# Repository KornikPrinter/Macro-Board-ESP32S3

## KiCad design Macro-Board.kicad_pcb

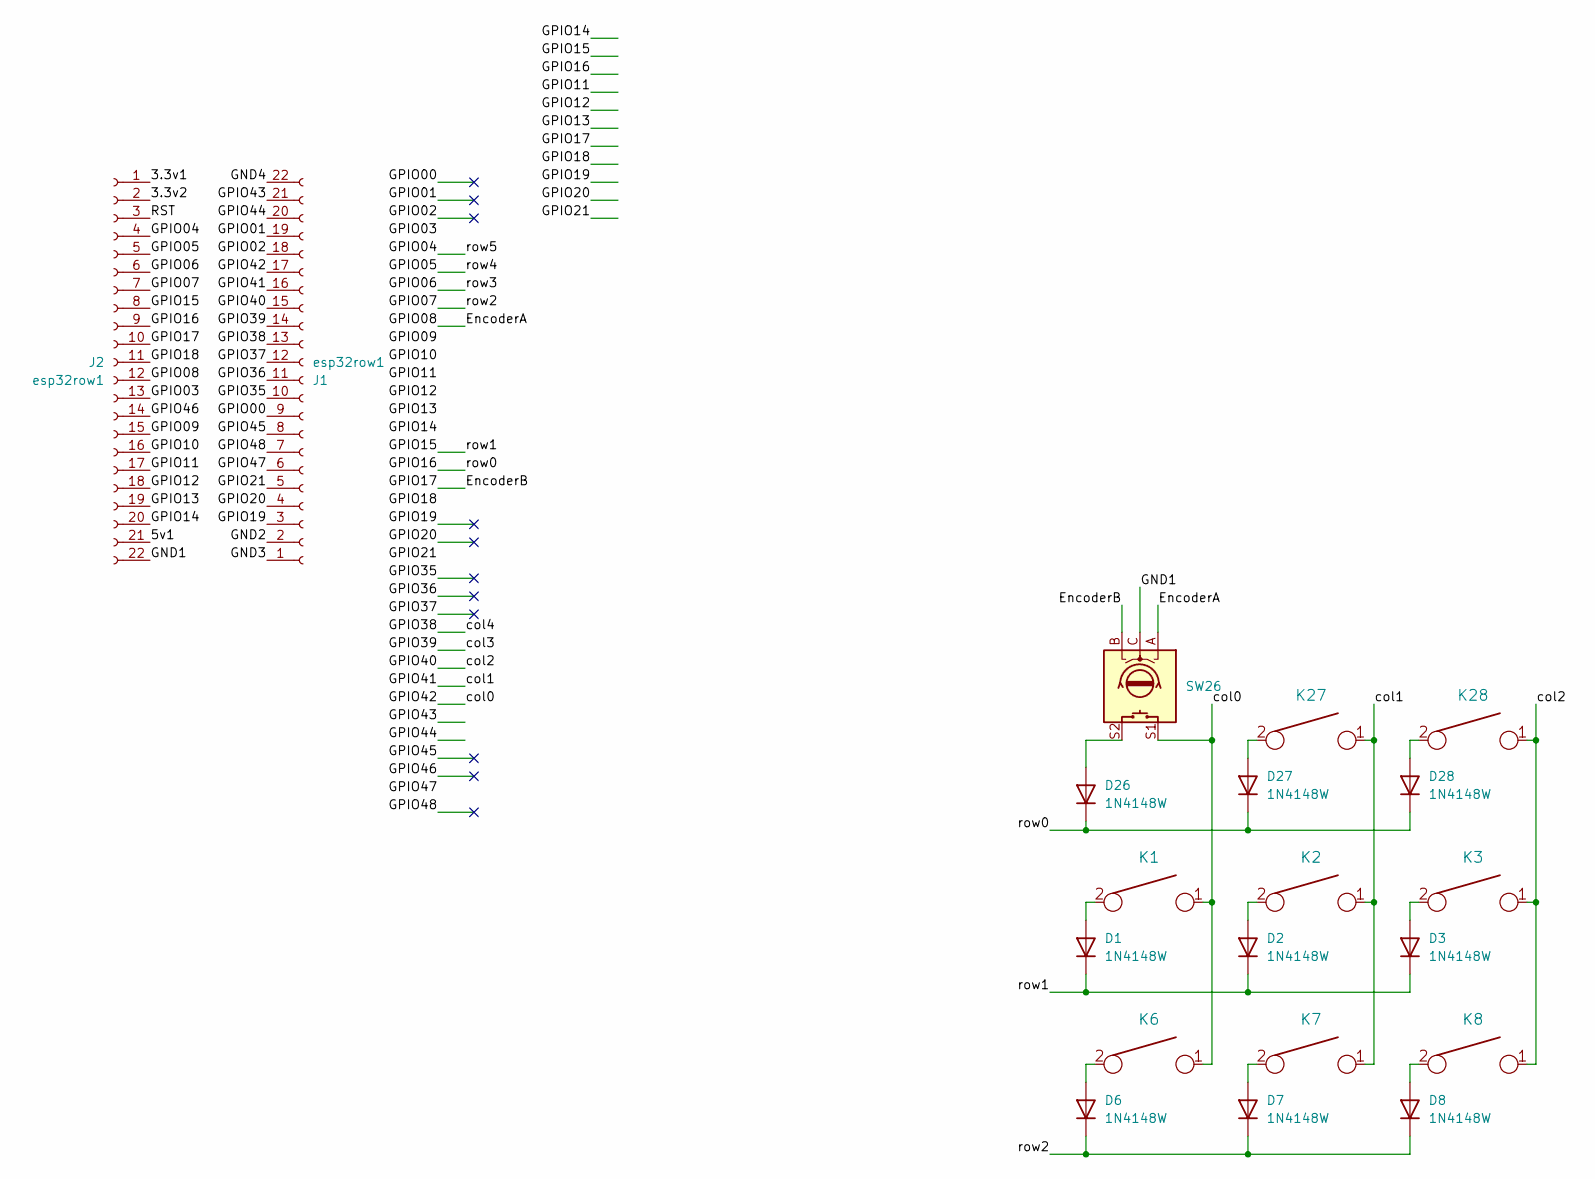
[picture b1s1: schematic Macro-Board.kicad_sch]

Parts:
D1, D2, D3, D6, D7, D8, D26, D27, D28: 1N4148W; D_SOD-123
J1, J2: esp32row1; PinSocket_1x22_P2.54mm_Vertical
K1, K2, K3, K6, K7, K8, K27, K28: KEYSW; SW_Hotswap_Kailh_MX_Plated_1.00u
SW26: RotaryEncoder_Alps_EC11E-Switch_Vertical_H20mm

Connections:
/3.3v1: J2.1
/3.3v2: J2.2
/5v1: J2.21
/EncoderA: J2.12, SW26.A
/EncoderB: J2.10, SW26.B
/GND1: J2.22, SW26.C
/GND2: J1.2
/GND3: J1.1
/GND4: J1.22
/GPIO00: J1.9
/GPIO01: J1.19
/GPIO02: J1.18
/GPIO03: J2.13
/GPIO04: J2.4
/GPIO05: J2.5
/GPIO06: J2.6
/GPIO07: D6.1 (K), D7.1 (K), D8.1 (K), J2.7
/GPIO09: J2.15
/GPIO10: J2.16
/GPIO11: J2.17
/GPIO12: J2.18
/GPIO13: J2.19
/GPIO14: J2.20
/GPIO15: D1.1 (K), D2.1 (K), D3.1 (K), J2.8
/GPIO16: D26.1 (K), D27.1 (K), D28.1 (K), J2.9
/GPIO18: J2.11
/GPIO19: J1.3
/GPIO20: J1.4
/GPIO21: J1.5
/GPIO35: J1.10
/GPIO36: J1.11
/GPIO37: J1.12
/GPIO38: J1.13
/GPIO39: J1.14
/GPIO40: J1.15, K3.1, K8.1, K28.1
/GPIO41: J1.16, K2.1, K7.1, K27.1
/GPIO42: J1.17, K1.1, K6.1, SW26.S1
/GPIO43: J1.21
/GPIO44: J1.20
/GPIO45: J1.8
/GPIO46: J2.14
/GPIO47: J1.6
/GPIO48: J1.7
/RST: J2.3
unnamed: D1.2 (A), K1.2
unnamed: D2.2 (A), K2.2
unnamed: D3.2 (A), K3.2
unnamed: D6.2 (A), K6.2
unnamed: D7.2 (A), K7.2
unnamed: D8.2 (A), K8.2
unnamed: D26.2 (A), SW26.S2
unnamed: D27.2 (A), K27.2
unnamed: D28.2 (A), K28.2

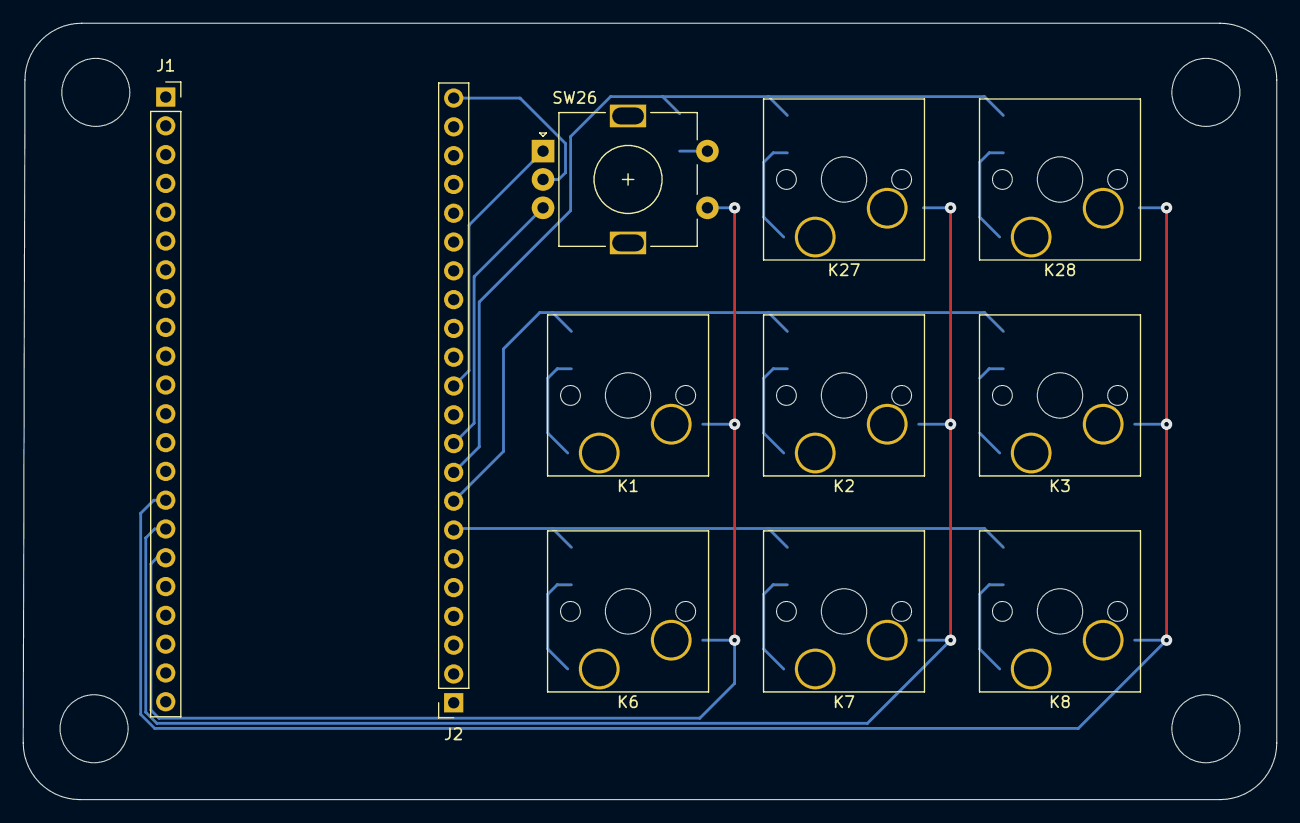
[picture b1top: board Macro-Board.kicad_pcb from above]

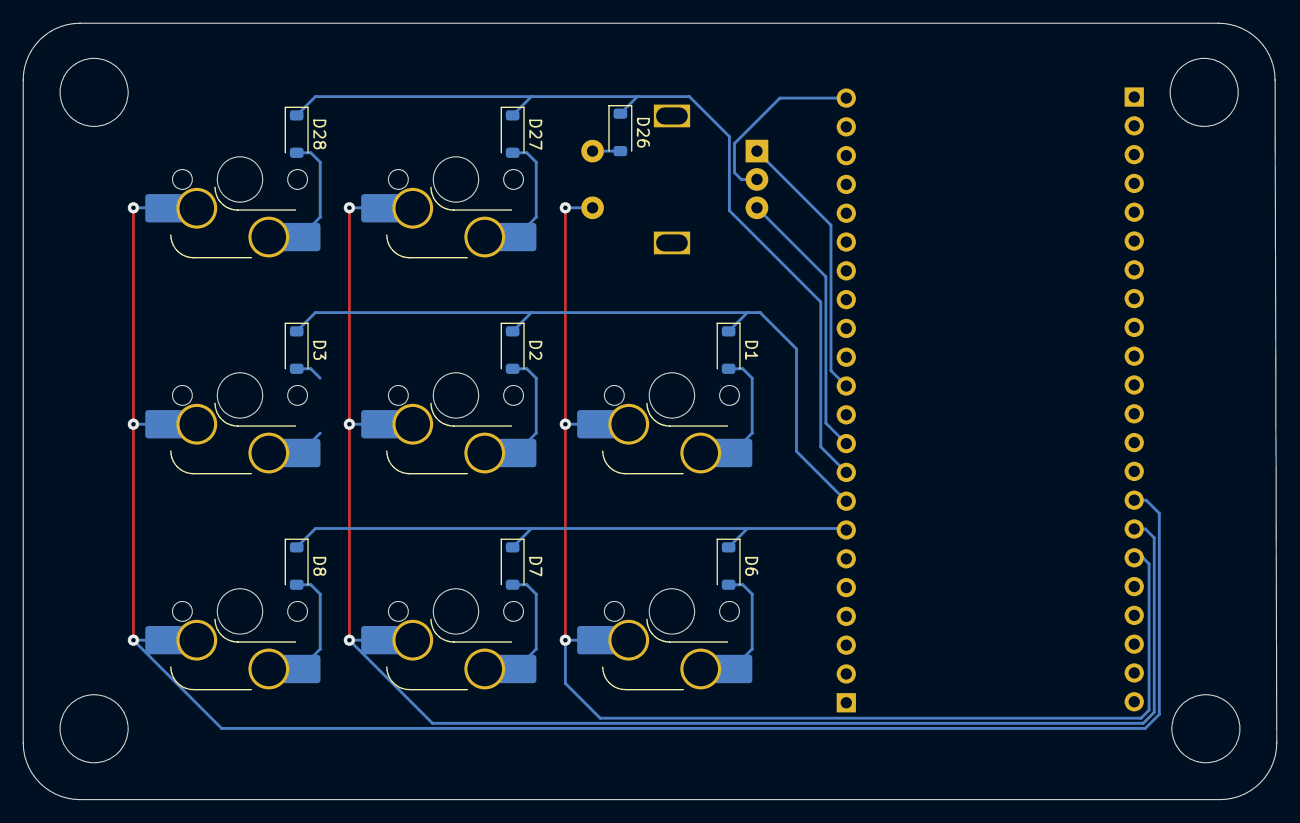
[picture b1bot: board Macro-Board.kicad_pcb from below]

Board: 2 copper layers, 110.6 x 68.5 mm, 20 parts (9 on the bottom side), 18 nets.

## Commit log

2026-03-23 Added PCB Edge + Updated Encoder Library
2026-04-08 PC modifications ffs
2026-04-13 Idfk
2026-04-16 cosmetic changes
2026-04-29 3x3 mod
